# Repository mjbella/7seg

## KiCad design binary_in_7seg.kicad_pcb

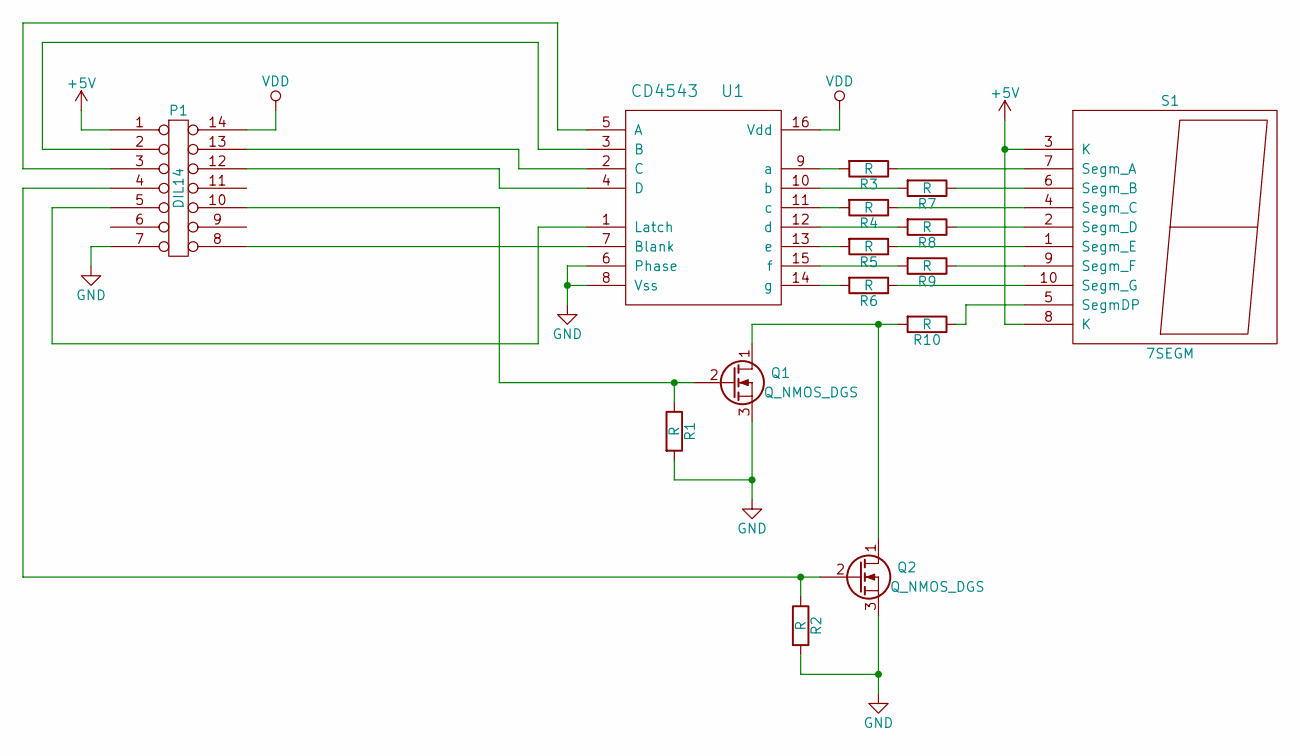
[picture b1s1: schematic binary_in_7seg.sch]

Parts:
P1: DIL14; DIP-14_W7.62mm
Q1, Q2: Q_NMOS_DGS; SOT-323
R1, R2, R3, R4, R5, R6, R7, R8, R9, R10: R; R_0402
S1: 7SEGM; 7SEGMENT-LED__HDSM531_HDSM533_SMD
U1: CD4543; TSSOP-16_4.4x5mm_Pitch0.65mm

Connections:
+5V: P1.1, S1.3 (K), S1.8 (K)
GND: P1.7, Q1.3 (S), Q2.3 (S), R1.2, R2.2, U1.6 (Phase), U1.8 (Vss)
unnamed: P1.2, U1.3 (B)
unnamed: P1.3, U1.5 (A)
unnamed: P1.4, Q2.2 (G), R2.1
unnamed: P1.5, U1.1 (Latch)
unnamed: P1.8, U1.7 (Blank)
unnamed: P1.10, Q1.2 (G), R1.1
unnamed: P1.12, U1.4 (D)
unnamed: P1.13, U1.2 (C)
unnamed: Q1.1 (D), Q2.1 (D), R10.2
unnamed: R3.1, S1.7 (Segm_A)
unnamed: R3.2, U1.9 (a)
unnamed: R4.1, S1.4 (Segm_C)
unnamed: R4.2, U1.11 (c)
unnamed: R5.1, S1.1 (Segm_E)
unnamed: R5.2, U1.13 (e)
unnamed: R6.1, S1.10 (Segm_G)
unnamed: R6.2, U1.14 (g)
unnamed: R7.1, S1.6 (Segm_B)
unnamed: R7.2, U1.10 (b)
unnamed: R8.1, S1.2 (Segm_D)
unnamed: R8.2, U1.12 (d)
unnamed: R9.1, S1.9 (Segm_F)
unnamed: R9.2, U1.15 (f)
unnamed: R10.1, S1.5 (SegmDP)
VDD: P1.14, U1.16 (Vdd)

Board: 2 copper layers, 15 parts (0 on the bottom side), 27 nets, no tracks yet.

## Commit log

2016-09-19 Filled in more of the schematic
2016-09-19 Added decimal point input
2016-09-19 Moved input connector symbol
2016-09-19 Starting layout
